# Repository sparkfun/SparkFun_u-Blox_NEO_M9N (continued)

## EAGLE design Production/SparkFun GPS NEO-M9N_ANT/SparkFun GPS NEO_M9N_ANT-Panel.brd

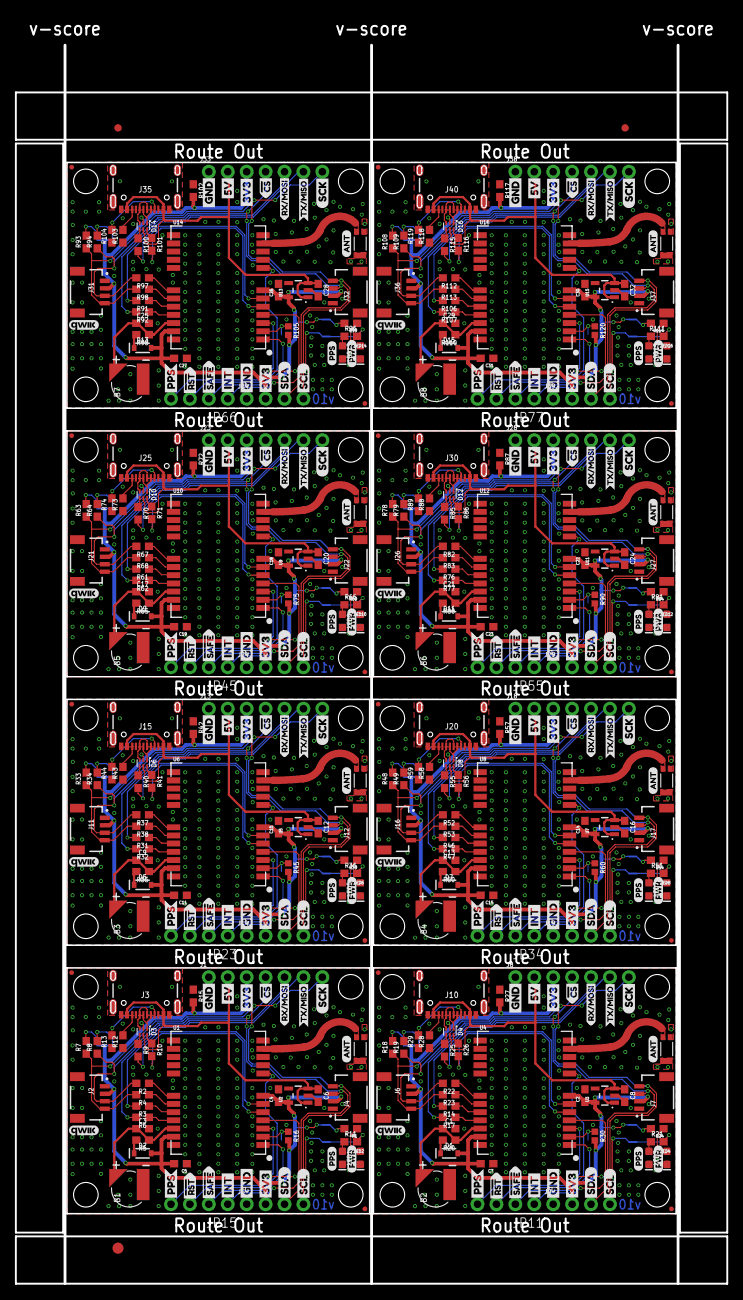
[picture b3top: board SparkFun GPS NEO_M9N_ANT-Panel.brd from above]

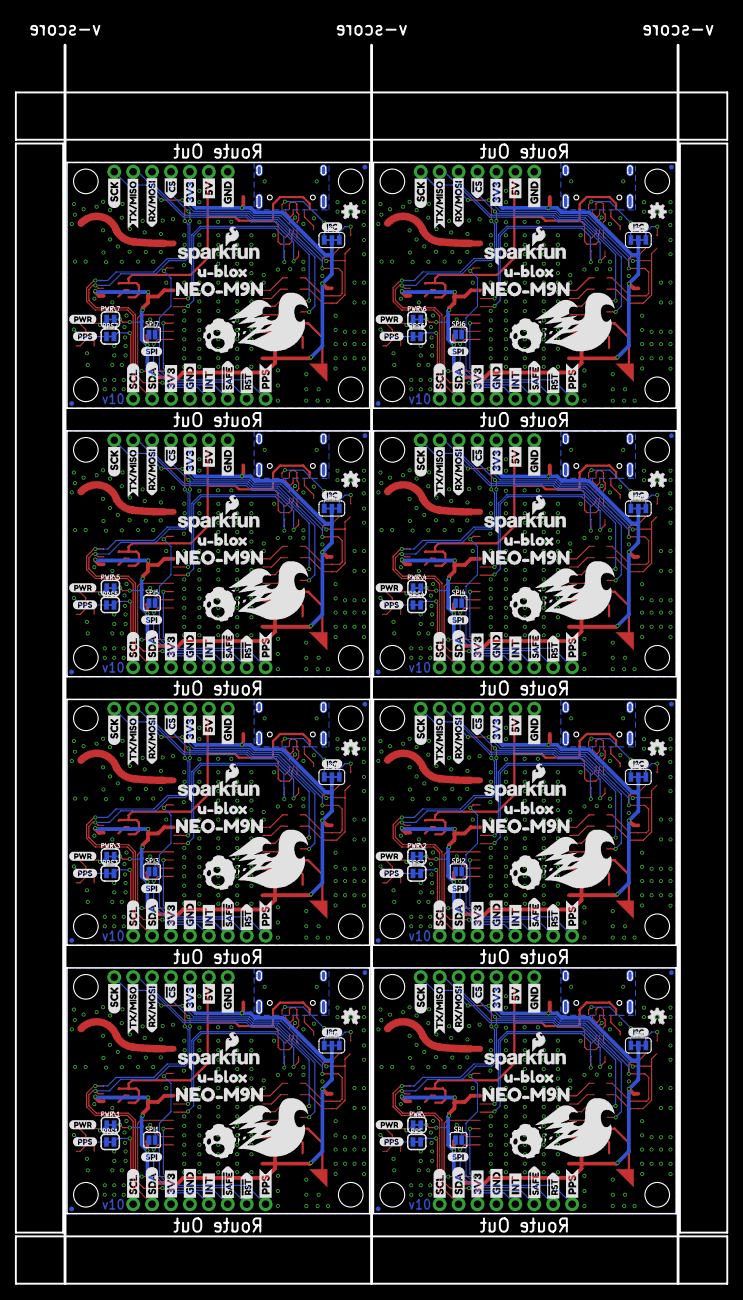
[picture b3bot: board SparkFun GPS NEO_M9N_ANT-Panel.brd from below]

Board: 2 copper layers, 95.5 x 166.3 mm, 707 parts (240 on the bottom side), 272 nets.

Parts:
B1, B2, B3, B4, B5, B6, B7, B8: 6.8MM_COIN_CELL; ML414H_IV01E
C1, C2, C3, C4, C6, C8, C9, C10, C12, C13, C14, C16, C17, C18, C20, C21, C22, C24, C25, C26, C28, C29, C30, C32: 1.0uF; 0603
C5, C7, C11, C15, C19, C23, C27, C31: 0.1uF; 0603
D1, D2, D5, D7, D9, D11, D13, D15: 0.5A/40V/420mV; SOD-323
D3, D4, D6, D8, D10, D12, D14, D16: PRTR5V0U2F; SOT886
E$1, E$2: FIDUCIAL-1X2
E$3: FIDUCIAL-1.5X3
J1, J8, J13, J18, J23, J28, J33, J38: 1X07_NO_SILK
J2, J4, J6, J7, J11, J12, J16, J17, J21, J22, J26, J27, J31, J32, J36, J37: Qwiic Right Angle; JST04_1MM_RA
J3, J10, J15, J20, J25, J30, J35, J40: USB-C-16P
J5, J9, J14, J19, J24, J29, J34, J39: 1X04_NO_SILK
JP1, JP2, JP9, JP10, JP12, JP13, JP20, JP22, JP24, JP25, JP31, JP32, JP33, JP35, JP36, JP41, JP43, JP44, JP46, JP47, JP53, JP54, JP56, JP57, JP64, JP65, JP67, JP68, JP75, JP76, JP91, JP101: STAND-OFF
JP3, JP4, JP7, JP8, JP14, JP16, JP18, JP19, JP21, JP26, JP27, JP29, JP30, JP37, JP38, JP40, JP42, JP48, JP49, JP51, JP52, JP58, JP59, JP61, JP62, JP63, JP69, JP70, JP71, JP73, JP74, JP81: FIDUCIALUFIDUCIAL; MICRO-FIDUCIAL
JP5, JP6, JP17, JP28, JP39, JP50, JP60, JP72: JUMPER-SMT_3_2-NC_TRACE_SILK; SMT-JUMPER_3_2-NC_TRACE_SILK
JP11, JP15, JP23, JP34, JP45, JP55, JP66, JP77: 1X04_NO_SILK
LED1, LED3, LED5, LED7, LED9, LED11, LED13, LED15: BLUE; LED-0603
LED2, LED4, LED6, LED8, LED10, LED12, LED14, LED16: RED; LED-0603
LOGO1, LOGO3, LOGO5, LOGO7, LOGO9, LOGO11, LOGO13, LOGO15: OSHW-LOGOMINI; OSHW-LOGO-MINI
LOGO2, LOGO4, LOGO6, LOGO8, LOGO10, LOGO12, LOGO14, LOGO16: SFE_LOGO_NAME_FLAME.1_INCH; SFE_LOGO_NAME_FLAME_.1
PPS, PPS1, PPS2, PPS3, PPS4, PPS5, PPS6, PPS7: JUMPER-SMT_2_NC_TRACE_SILK; SMT-JUMPER_2_NC_TRACE_SILK
PWR\, PWR\1, PWR\2, PWR\3, PWR\4, PWR\5, PWR\6, PWR\7: JUMPER-SMT_2_NC_TRACE_SILK; SMT-JUMPER_2_NC_TRACE_SILK
R1, R5, R11, R20, R21, R24, R35, R36, R39, R50, R51, R54, R65, R66, R69, R80, R81, R84, R95, R96, R99, R110, R111, R114: 1k; 0603
R2, R3, R4, R6, R14, R17, R22, R23, R31, R32, R37, R38, R46, R47, R52, R53, R61, R62, R67, R68, R76, R77, R82, R83, R91, R92, R97, R98, R106, R107, R112, R113: 33; 0603
R7, R8, R18, R19, R33, R34, R48, R49, R63, R64, R78, R79, R93, R94, R108, R109: 2.2k; 0603
R9, R10, R25, R26, R40, R41, R55, R56, R70, R71, R85, R86, R100, R101, R115, R116: 27; 0603
R12, R13, R28, R29, R43, R44, R58, R59, R73, R74, R88, R89, R103, R104, R118, R119: 5.1k; 0603
R15, R27, R42, R57, R72, R87, R102, R117: 100k; 0603
R16, R30, R45, R60, R75, R90, R105, R120: 10k; 0402
SPI, SPI1, SPI2, SPI3, SPI4, SPI5, SPI6, SPI7: JUMPER-SMT_2_NO_SILK; SMT-JUMPER_2_NO_SILK
U1, U4, U6, U8, U10, U12, U14, U16: U-BLOX_NEO-M9N; NEO-M9N
U2, U3, U5, U7, U9, U11, U13, U15: 3.3V; SOT23-5
U$1, U$4, U$25, U$28, U$83, U$85, U$124, U$126, U$165, U$167, U$206, U$208, U$247, U$249, U$288, U$290: SDA-[)
U$2, U$76, U$117, U$158, U$199, U$240, U$281, U$322: NEO#M9N1
U$3, U$5, U$27, U$29, U$84, U$86, U$125, U$127, U$166, U$168, U$207, U$209, U$248, U$250, U$289, U$291: SCL-[)
U$6, U$7, U$30, U$32, U$57, U$58, U$60, U$61, U$87, U$88, U$102, U$103, U$128, U$129, U$143, U$144, U$169, U$170, U$184, U$185, U$210, U$211, U$225, U$226, U$251, U$252, U$266, U$267, U$292, U$293, U$307, U$308: 3V3-04
U$8, U$9, U$33, U$42, U$59, U$62, U$63, U$64, U$89, U$90, U$104, U$105, U$130, U$131, U$145, U$146, U$171, U$172, U$186, U$187, U$212, U$213, U$227, U$228, U$253, U$254, U$268, U$269, U$294, U$295, U$309, U$310: GND-04
U$10, U$45, U$91, U$132, U$173, U$214, U$255, U$296: I_SUPER2_C-()-03
U$11, U$77, U$118, U$159, U$200, U$241, U$282, U$323: SPI1
U$12, U$52, U$56, U$79, U$101, U$120, U$142, U$161, U$183, U$202, U$224, U$243, U$265, U$284, U$306, U$325: PPS0
U$13, U$81, U$122, U$163, U$204, U$245, U$286, U$327: ANT0
U$14, U$78, U$119, U$160, U$201, U$242, U$283, U$324: QWIIC_4MM
U$15, U$16, U$46, U$47, U$92, U$93, U$133, U$134, U$174, U$175, U$215, U$216, U$256, U$257, U$297, U$298: INT8
U$17, U$80, U$121, U$162, U$203, U$244, U$285, U$326: PWR1
U$18, U$65, U$106, U$147, U$188, U$229, U$270, U$311: PWR-()-03
U$19, U$20, U$66, U$67, U$107, U$108, U$148, U$149, U$189, U$190, U$230, U$231, U$271, U$272, U$312, U$313: 5V
U$21, U$82, U$123, U$164, U$205, U$246, U$287, U$328: NEO_GPS_BOARD_SILK_FINAL#03#JPG
U$22, U$48, U$94, U$135, U$176, U$217, U$258, U$299: U#BLOX3
U$23, U$24, U$68, U$69, U$109, U$110, U$150, U$151, U$191, U$192, U$232, U$233, U$273, U$274, U$314, U$315: CS#-<]
U$26, U$72, U$113, U$154, U$195, U$236, U$277, U$318: RX#MOSI2
U$31, U$73, U$114, U$155, U$196, U$237, U$278, U$319: RX#MOSI3
U$34, U$74, U$115, U$156, U$197, U$238, U$279, U$320: TX#MISO0
U$35, U$36, U$49, U$50, U$95, U$96, U$136, U$137, U$177, U$178, U$218, U$219, U$259, U$260, U$300, U$301: #RST3
U$37, U$75, U$116, U$157, U$198, U$239, U$280, U$321: TX#MISO1
U$38, U$41, U$70, U$71, U$111, U$112, U$152, U$153, U$193, U$194, U$234, U$235, U$275, U$276, U$316, U$317: SCK-(]-04
U$39, U$40, U$51, U$53, U$97, U$98, U$138, U$139, U$179, U$180, U$220, U$221, U$261, U$262, U$302, U$303: #SAFE1
U$43, U$44, U$54, U$55, U$99, U$100, U$140, U$141, U$181, U$182, U$222, U$223, U$263, U$264, U$304, U$305: PPS5
Y1, Y2, Y3, Y4, Y5, Y6, Y7, Y8: GPS_CHIP_ANTENNAW3011; W3011

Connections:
3.3V: C4.1, C5.2, D2.A, J1.3, J2.2, J4.2, J5.2, JP5.2, PWR\.2, R15.2, R16.2, U1.7, U1.23, U2.5
3.3V1: C2.1, C7.2, D1.A, J6.2, J7.2, J8.3, J9.2, JP6.2, PWR\1.2, R27.2, R30.2, U3.5, U4.7, U4.23
3.3V2: C10.1, C11.2, D5.A, J11.2, J12.2, J13.3, J14.2, JP17.2, PWR\2.2, R42.2, R45.2, U5.5, U6.7, U6.23
3.3V3: C14.1, C15.2, D7.A, J16.2, J17.2, J18.3, J19.2, JP28.2, PWR\3.2, R57.2, R60.2, U7.5, U8.7, U8.23
3.3V4: C18.1, C19.2, D9.A, J21.2, J22.2, J23.3, J24.2, JP39.2, PWR\4.2, R72.2, R75.2, U9.5, U10.7, U10.23
3.3V5: C22.1, C23.2, D11.A, J26.2, J27.2, J28.3, J29.2, JP50.2, PWR\5.2, R87.2, R90.2, U11.5, U12.7, U12.23
3.3V6: C26.1, C27.2, D13.A, J31.2, J32.2, J33.3, J34.2, JP60.2, PWR\6.2, R102.2, R105.2, U13.5, U14.7, U14.23
3.3V7: C30.1, C31.2, D15.A, J36.2, J37.2, J38.3, J39.2, JP72.2, PWR\7.2, R117.2, R120.2, U15.5, U16.7, U16.23
5V: C6.1, D3.5, J1.2, J3.VBUS1, J3.VBUS2, U2.1, U2.3
5V1: C8.1, D4.5, J8.2, J10.VBUS1, J10.VBUS2, U3.1, U3.3
5V2: C12.1, D6.5, J13.2, J15.VBUS1, J15.VBUS2, U5.1, U5.3
5V3: C16.1, D8.5, J18.2, J20.VBUS1, J20.VBUS2, U7.1, U7.3
5V4: C20.1, D10.5, J23.2, J25.VBUS1, J25.VBUS2, U9.1, U9.3
5V5: C24.1, D12.5, J28.2, J30.VBUS1, J30.VBUS2, U11.1, U11.3
5V6: C28.1, D14.5, J33.2, J35.VBUS1, J35.VBUS2, U13.1, U13.3
5V7: C32.1, D16.5, J38.2, J40.VBUS1, J40.VBUS2, U15.1, U15.3
!RESET: JP15.3, U1.8
!RESET1: JP11.3, U4.8
!RESET2: JP23.3, U6.8
!RESET3: JP34.3, U8.8
!RESET4: JP45.3, U10.8
!RESET5: JP55.3, U12.8
!RESET6: JP66.3, U14.8
!RESET7: JP77.3, U16.8
!SAFE: JP15.2, U1.1
!SAFE1: JP11.2, U4.1
!SAFE2: JP23.2, U6.1
!SAFE3: JP34.2, U8.1
!SAFE4: JP45.2, U10.1
!SAFE5: JP55.2, U12.1
!SAFE6: JP66.2, U14.1
!SAFE7: JP77.2, U16.1
BACKUP: B1.+, C3.1, R5.1, U1.22
BACKUP1: B2.+, C1.1, R20.1, U4.22
BACKUP2: B3.+, C9.1, R35.1, U6.22
BACKUP3: B4.+, C13.1, R50.1, U8.22
BACKUP4: B5.+, C17.1, R65.1, U10.22
BACKUP5: B6.+, C21.1, R80.1, U12.22
BACKUP6: B7.+, C25.1, R95.1, U14.22
BACKUP7: B8.+, C29.1, R110.1, U16.22
D+: D3.4, R9.1
D+1: D4.4, R25.1
D+2: D6.4, R40.1
D+3: D8.4, R55.1
D+4: D10.4, R70.1
D+5: D12.4, R85.1
D+6: D14.4, R100.1
D+7: D16.4, R115.1
D-: D3.6, R10.1
D-1: D4.6, R26.1
D-2: D6.6, R41.1
D-3: D8.6, R56.1
D-4: D10.6, R71.1
D-5: D12.6, R86.1
D-6: D14.6, R101.1
D-7: D16.6, R116.1
D_SEL: R16.1, SPI.2, U1.2
D_SEL1: R30.1, SPI1.2, U4.2
D_SEL2: R45.1, SPI2.2, U6.2
D_SEL3: R60.1, SPI3.2, U8.2
D_SEL4: R75.1, SPI4.2, U10.2
D_SEL5: R90.1, SPI5.2, U12.2
D_SEL6: R105.1, SPI6.2, U14.2
D_SEL7: R120.1, SPI7.2, U16.2
GND: B1.-, C3.2, C4.2, C5.1, C6.2, D3.2, J1.1, J2.1, J3.GND, J3.GND2, J4.1, J5.1, LED1.C, LED2.C, R12.1, R13.1, R15.1, SPI.1, U1.10, U1.12, U1.13, U1.24, U2.2, Y1.2, Y1.3
GND1: B2.-, C1.2, C2.2, C7.1, C8.2, D4.2, J6.1, J7.1, J8.1, J9.1, J10.GND, J10.GND2, LED3.C, LED4.C, R27.1, R28.1, R29.1, SPI1.1, U3.2, U4.10, U4.12, U4.13, U4.24, Y2.2, Y2.3
GND2: B3.-, C9.2, C10.2, C11.1, C12.2, D6.2, J11.1, J12.1, J13.1, J14.1, J15.GND, J15.GND2, LED5.C, LED6.C, R42.1, R43.1, R44.1, SPI2.1, U5.2, U6.10, U6.12, U6.13, U6.24, Y3.2, Y3.3
GND3: B4.-, C13.2, C14.2, C15.1, C16.2, D8.2, J16.1, J17.1, J18.1, J19.1, J20.GND, J20.GND2, LED7.C, LED8.C, R57.1, R58.1, R59.1, SPI3.1, U7.2, U8.10, U8.12, U8.13, U8.24, Y4.2, Y4.3
GND4: B5.-, C17.2, C18.2, C19.1, C20.2, D10.2, J21.1, J22.1, J23.1, J24.1, J25.GND, J25.GND2, LED9.C, LED10.C, R72.1, R73.1, R74.1, SPI4.1, U9.2, U10.10, U10.12, U10.13, U10.24, Y5.2, Y5.3
GND5: B6.-, C21.2, C22.2, C23.1, C24.2, D12.2, J26.1, J27.1, J28.1, J29.1, J30.GND, J30.GND2, LED11.C, LED12.C, R87.1, R88.1, R89.1, SPI5.1, U11.2, U12.10, U12.12, U12.13, U12.24, Y6.2, Y6.3
GND6: B7.-, C25.2, C26.2, C27.1, C28.2, D14.2, J31.1, J32.1, J33.1, J34.1, J35.GND, J35.GND2, LED13.C, LED14.C, R102.1, R103.1, R104.1, SPI6.1, U13.2, U14.10, U14.12, U14.13, U14.24, Y7.2, Y7.3
GND7: B8.-, C29.2, C30.2, C31.1, C32.2, D16.2, J36.1, J37.1, J38.1, J39.1, J40.GND, J40.GND2, LED15.C, LED16.C, R117.1, R118.1, R119.1, SPI7.1, U15.2, U16.10, U16.12, U16.13, U16.24, Y8.2, Y8.3
GPS_ANT1: U1.11, Y1.1
GPS_ANT2: U4.11, Y2.1
GPS_ANT3: U6.11, Y3.1
GPS_ANT4: U8.11, Y4.1
GPS_ANT5: U10.11, Y5.1
GPS_ANT6: U12.11, Y6.1
GPS_ANT7: U14.11, Y7.1
GPS_ANT8: U16.11, Y8.1
INT: JP15.1, U1.4
INT1: JP11.1, U4.4
INT2: JP23.1, U6.4
INT3: JP34.1, U8.4
INT4: JP45.1, U10.4
INT5: JP55.1, U12.4
INT6: JP66.1, U14.4
INT7: JP77.1, U16.4
unnamed: PWR\.1, R1.2
unnamed: LED1.A, R11.1
unnamed: JP6.1, R19.2
unnamed: PPS.1, R11.2
unnamed: JP5.1, R8.2
unnamed: D2.C, R5.2
unnamed: J3.B5, R12.2
unnamed: JP5.3, R7.2
unnamed: J3.A5, R13.2
unnamed: LED2.A, R1.1
unnamed: R9.2, U1.6
unnamed: R10.2, U1.5
unnamed: JP6.3, R18.2
unnamed: LED3.A, R21.1
unnamed: PPS1.1, R21.2
unnamed: D1.C, R20.2
unnamed: LED4.A, R24.1
unnamed: R25.2, U4.6
unnamed: R26.2, U4.5
unnamed: PWR\1.1, R24.2
unnamed: J10.B5, R28.2
unnamed: J10.A5, R29.2
unnamed: JP17.1, R34.2
unnamed: JP17.3, R33.2
unnamed: LED5.A, R36.1
unnamed: PPS2.1, R36.2
unnamed: D5.C, R35.2
unnamed: LED6.A, R39.1
unnamed: R40.2, U6.6
unnamed: R41.2, U6.5
unnamed: PWR\2.1, R39.2
unnamed: J15.B5, R43.2
unnamed: J15.A5, R44.2
unnamed: JP28.1, R49.2
unnamed: JP28.3, R48.2
unnamed: LED7.A, R51.1
unnamed: PPS3.1, R51.2
unnamed: D7.C, R50.2
unnamed: LED8.A, R54.1
unnamed: R55.2, U8.6
unnamed: R56.2, U8.5
unnamed: PWR\3.1, R54.2
unnamed: J20.B5, R58.2
unnamed: J20.A5, R59.2
unnamed: JP39.1, R64.2
unnamed: JP39.3, R63.2
unnamed: LED9.A, R66.1
unnamed: PPS4.1, R66.2
unnamed: D9.C, R65.2
unnamed: LED10.A, R69.1
unnamed: R70.2, U10.6
unnamed: R71.2, U10.5
unnamed: PWR\4.1, R69.2
unnamed: J25.B5, R73.2
unnamed: J25.A5, R74.2
unnamed: JP50.1, R79.2
unnamed: JP50.3, R78.2
unnamed: LED11.A, R81.1
unnamed: PPS5.1, R81.2
unnamed: D11.C, R80.2
unnamed: LED12.A, R84.1
unnamed: R85.2, U12.6
unnamed: R86.2, U12.5
unnamed: PWR\5.1, R84.2
unnamed: J30.B5, R88.2
unnamed: J30.A5, R89.2
unnamed: JP60.1, R94.2
unnamed: JP60.3, R93.2
unnamed: LED13.A, R96.1
unnamed: PPS6.1, R96.2
unnamed: D13.C, R95.2
unnamed: LED14.A, R99.1
unnamed: R100.2, U14.6
unnamed: R101.2, U14.5
unnamed: PWR\6.1, R99.2
unnamed: J35.B5, R103.2
unnamed: J35.A5, R104.2
unnamed: JP72.1, R109.2
unnamed: JP72.3, R108.2
unnamed: LED15.A, R111.1
unnamed: PPS7.1, R111.2
unnamed: D15.C, R110.2
unnamed: LED16.A, R114.1
unnamed: R115.2, U16.6
unnamed: R116.2, U16.5
unnamed: PWR\7.1, R114.2
unnamed: J40.B5, R118.2
unnamed: J40.A5, R119.2
PPS: JP15.4, PPS.2, U1.3
PPS1: JP11.4, PPS1.2, U4.3
PPS2: JP23.4, PPS2.2, U6.3
PPS3: JP34.4, PPS3.2, U8.3
PPS4: JP45.4, PPS4.2, U10.3
PPS5: JP55.4, PPS5.2, U12.3
PPS6: JP66.4, PPS6.2, U14.3
PPS7: JP77.4, PPS7.2, U16.3
RXI/MOSI: J1.5, R6.2
RXI/MOSI1: J8.5, R17.2
RXI/MOSI2: J13.5, R32.2
RXI/MOSI3: J18.5, R47.2
RXI/MOSI4: J23.5, R62.2
RXI/MOSI5: J28.5, R77.2
RXI/MOSI6: J33.5, R92.2
RXI/MOSI7: J38.5, R107.2
RXLV: R6.1, U1.21
RXLV1: R17.1, U4.21
RXLV2: R32.1, U6.21
RXLV3: R47.1, U8.21
RXLV4: R62.1, U10.21
RXLV5: R77.1, U12.21
RXLV6: R92.1, U14.21
RXLV7: R107.1, U16.21
SCL/SCK: J1.7, J2.4, J4.4, J5.4, R4.2, R7.1
SCL/SCK1: J6.4, J7.4, J8.7, J9.4, R18.1, R23.2
SCL/SCK2: J11.4, J12.4, J13.7, J14.4, R33.1, R38.2
SCL/SCK3: J16.4, J17.4, J18.7, J19.4, R48.1, R53.2
SCL/SCK4: J21.4, J22.4, J23.7, J24.4, R63.1, R68.2
SCL/SCK5: J26.4, J27.4, J28.7, J29.4, R78.1, R83.2
SCL/SCK6: J31.4, J32.4, J33.7, J34.4, R93.1, R98.2
SCL/SCK7: J36.4, J37.4, J38.7, J39.4, R108.1, R113.2
SCL_LV: R4.1, U1.19
SCL_LV1: R23.1, U4.19
SCL_LV2: R38.1, U6.19
SCL_LV3: R53.1, U8.19
SCL_LV4: R68.1, U10.19
SCL_LV5: R83.1, U12.19
SCL_LV6: R98.1, U14.19
SCL_LV7: R113.1, U16.19
SDA/!CS: J1.4, J2.3, J4.3, J5.3, R2.2, R8.1
SDA/!CS1: J6.3, J7.3, J8.4, J9.3, R19.1, R22.2
SDA/!CS2: J11.3, J12.3, J13.4, J14.3, R34.1, R37.2
SDA/!CS3: J16.3, J17.3, J18.4, J19.3, R49.1, R52.2
SDA/!CS4: J21.3, J22.3, J23.4, J24.3, R64.1, R67.2
SDA/!CS5: J26.3, J27.3, J28.4, J29.3, R79.1, R82.2
SDA/!CS6: J31.3, J32.3, J33.4, J34.3, R94.1, R97.2
SDA/!CS7: J36.3, J37.3, J38.4, J39.3, R109.1, R112.2
SDA_LV: R2.1, U1.18
SDA_LV1: R22.1, U4.18
SDA_LV2: R37.1, U6.18
SDA_LV3: R52.1, U8.18
SDA_LV4: R67.1, U10.18
SDA_LV5: R82.1, U12.18
SDA_LV6: R97.1, U14.18
SDA_LV7: R112.1, U16.18
SHLD: J3.SHLD1, J3.SHLD2, J3.SHLD3, J3.SHLD4, J3.SHLD5, J3.SHLD6, J3.SHLD7, J3.SHLD8
SHLD1: J10.SHLD1, J10.SHLD2, J10.SHLD3, J10.SHLD4, J10.SHLD5, J10.SHLD6, J10.SHLD7, J10.SHLD8
SHLD2: J15.SHLD1, J15.SHLD2, J15.SHLD3, J15.SHLD4, J15.SHLD5, J15.SHLD6, J15.SHLD7, J15.SHLD8
SHLD3: J20.SHLD1, J20.SHLD2, J20.SHLD3, J20.SHLD4, J20.SHLD5, J20.SHLD6, J20.SHLD7, J20.SHLD8
SHLD4: J25.SHLD1, J25.SHLD2, J25.SHLD3, J25.SHLD4, J25.SHLD5, J25.SHLD6, J25.SHLD7, J25.SHLD8
SHLD5: J30.SHLD1, J30.SHLD2, J30.SHLD3, J30.SHLD4, J30.SHLD5, J30.SHLD6, J30.SHLD7, J30.SHLD8
SHLD6: J35.SHLD1, J35.SHLD2, J35.SHLD3, J35.SHLD4, J35.SHLD5, J35.SHLD6, J35.SHLD7, J35.SHLD8
SHLD7: J40.SHLD1, J40.SHLD2, J40.SHLD3, J40.SHLD4, J40.SHLD5, J40.SHLD6, J40.SHLD7, J40.SHLD8
TXLV: R3.1, U1.20
TXLV1: R14.1, U4.20
TXLV2: R31.1, U6.20
TXLV3: R46.1, U8.20
TXLV4: R61.1, U10.20
TXLV5: R76.1, U12.20
TXLV6: R91.1, U14.20
TXLV7: R106.1, U16.20
TXO/MISO: J1.6, R3.2
TXO/MISO1: J8.6, R14.2
TXO/MISO2: J13.6, R31.2
TXO/MISO3: J18.6, R46.2
TXO/MISO4: J23.6, R61.2
TXO/MISO5: J28.6, R76.2
TXO/MISO6: J33.6, R91.2
TXO/MISO7: J38.6, R106.2
USB_D+: D3.3, J3.A6, J3.B6
USB_D+1: D4.3, J10.A6, J10.B6
USB_D+2: D6.3, J15.A6, J15.B6
USB_D+3: D8.3, J20.A6, J20.B6
USB_D+4: D10.3, J25.A6, J25.B6
USB_D+5: D12.3, J30.A6, J30.B6
USB_D+6: D14.3, J35.A6, J35.B6
USB_D+7: D16.3, J40.A6, J40.B6
USB_D-: D3.1, J3.A7, J3.B7
USB_D-1: D4.1, J10.A7, J10.B7
USB_D-2: D6.1, J15.A7, J15.B7
USB_D-3: D8.1, J20.A7, J20.B7
USB_D-4: D10.1, J25.A7, J25.B7
USB_D-5: D12.1, J30.A7, J30.B7
USB_D-6: D14.1, J35.A7, J35.B7
USB_D-7: D16.1, J40.A7, J40.B7

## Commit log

2019-08-27 Initial Commit: folders and datasheet
2019-08-27 Adds USB-C connector, removes some stat LEDs, adds power led jumper
2019-08-28 Initial issues dealt with, air wires etc
2019-08-28 Updates the order of the info boxes in the schematic, adds 10k pullup to D_SEL
2019-08-28 Routes 10k pullup resistor, adds labels, fixes air wires
2019-08-28 Adds gerber files
2019-09-05 Beings work on version with antenna
2019-09-05 Initial design for product with antenna
2019-09-05 Fixes small DRC problems, Adds silk to battery, adds production id to NEO-M9N chip
2019-09-05 Renames version with u.FL connector to reflect that it is the one with a u.FL
2019-09-11 Adds coplanar waveguide for antenna to antenna version, adds gerbers for uFL version
2019-09-11 Adds chip antenna documentation
2019-09-12 Changes trace for antenna to s-bend, adds silk to battery, adds vcc range to schematic, adjusts jumper
2019-09-12 Fixes some DRC error
2019-09-12 Adds gerbers for NEO-M9N with chip antenna
2019-09-13 Adds sweet silk to NEO board
2019-09-13 Adds sweet silk to Antenna design
2019-09-16 Updates both designs with 5.1k resistor in 0603 package
2019-09-17 Updates Antenna silk
2019-09-17 Moves little bits around
2019-09-17 Updates readme for both chips
2019-09-17 Fixes 5V line, changes version
2019-09-17 Missed version updated
2019-10-21 Moves production files around
2019-10-21 Updates the antenna version to have better ground pour on the antenna, and a better curve on the feed line
2019-10-21 Changes version to v02
2019-10-21 Creates prototype version without Qwiic connector near gps antenna
2019-10-21 Changes version on single-qwiic board to v03
2019-10-21 ....and now renames board files to proto3 to align with v03 copper and schematic text
2019-11-06 Removes VCC bias to antenna from antenna design
    * Deletes all gerber files related to prototypes
    * Moves GPS library out of the buzzard label folder
    * Deletes buzzard labels
2019-11-07 Updates Schematic to be more neat
2019-11-07 Moves cap by regulator ever so slightly to get cream from module out of keepout
2019-11-07 Moves left qwiic connector down to match right one, updates measures, moves some vias
2019-11-07 Fixes an air wire and wire stub
2019-11-07 Adds production panel gerbers
2020-01-03 Removes local eagle library and replaces part from that library with part from SparkFun Eagle Library
2020-09-30 Updates libs, adds SMA connector and rf bias circuit
2020-09-30 Routed updates USB footprint and SMA connector with its RF circuitry
2020-10-01 Restore chip antenna version, and moves SMA version to its' own folder
2020-10-01 Adds Silk to "LONG" SMA version, adds measures
2020-10-08 Updates SMD, SMA connector with new footprint
    * Fixes connector label in schematic
    * Fixes LED labels
    * Fixes TX/SDO label
    * Adds VCC Range to regulator
2020-10-12 Updates the SMD, SMA Connector with new footprint
2020-10-13 Adds some text for L1/L2 band support on the schematic
2020-10-15 Replaces 1x4 connectors with versions that don't have a SKU
2020-10-15 Removes unused SMA version
2020-10-15 Changes the "Long" version name to just "SMA"
2020-10-15 Changes to female SMD, SMA connector
2020-10-20 v10 panel
2020-10-21 Moves SMA production files to main production folder
2022-04-07 Fixes "u-blox" typos in schematic
2023-04-27 Update Datasheet
